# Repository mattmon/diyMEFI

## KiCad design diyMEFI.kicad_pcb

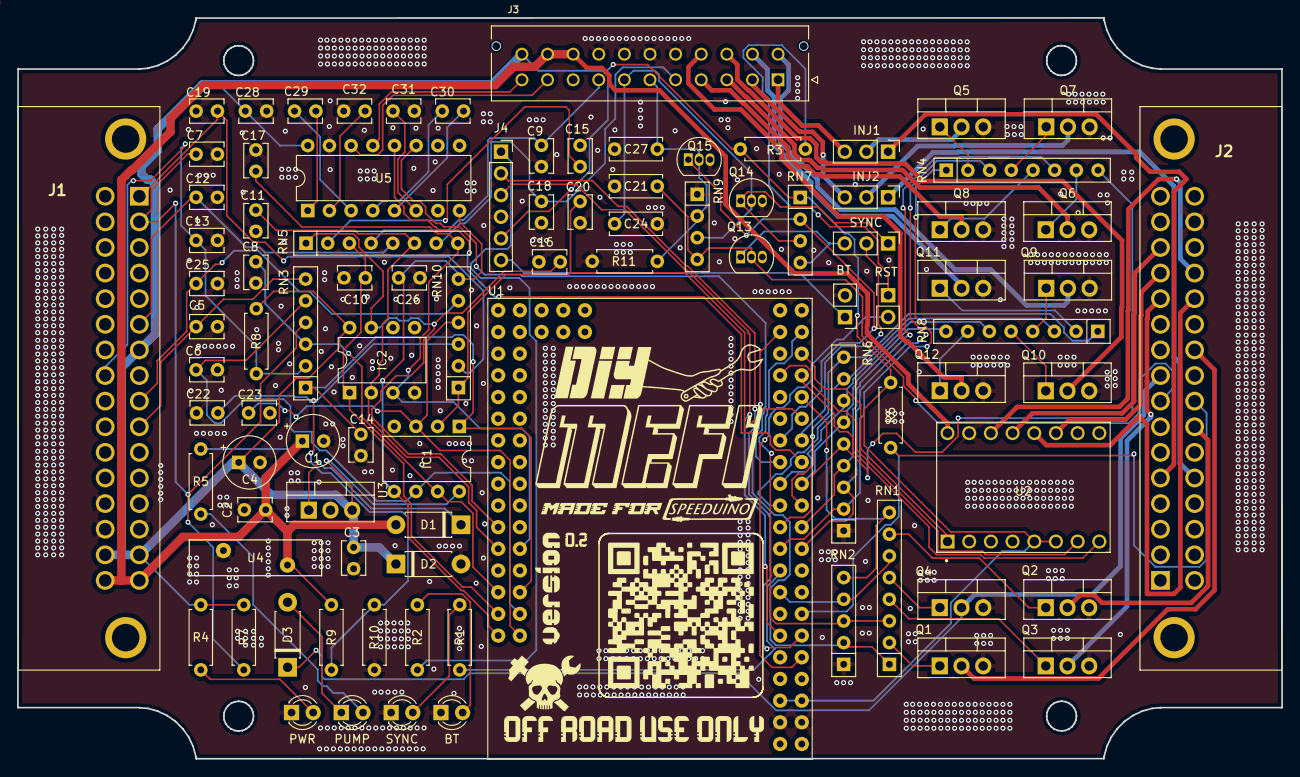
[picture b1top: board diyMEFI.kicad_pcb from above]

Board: 2 copper layers, 148.1 x 86.8 mm, 91 parts (0 on the bottom side), 101 nets.

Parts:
BT: Jumper_2_Open; PinHeader_1x02_P2.54mm_Vertical
BT#2: BLUE; LED_D3.0mm
C1: 10u; CP_Radial_Tantal_D6.0mm_P2.50mm
C2, C3, C5, C7, C9, C12, C13, C15, C18, C19, C22, C25: u1; C_Disc_D3.8mm_W2.6mm_P2.50mm
C4: 47u; CP_Radial_Tantal_D6.0mm_P2.50mm
C6, C8, C10, C11, C14, C16, C17, C20, C23, C26: u22; C_Disc_D3.8mm_W2.6mm_P2.50mm
C21, C24, C27: u1; C_Disc_D6.0mm_W2.5mm_P5.00mm
C28, C29, C30, C31, C32: 1uf; C_Disc_D3.8mm_W2.6mm_P2.50mm
D1: 1N5818; D_DO-41_SOD81_P7.62mm_Horizontal
D2: 1N5919BG; D_DO-41_SOD81_P7.62mm_Horizontal
D3: 1N4004; D_DO-41_SOD81_P7.62mm_Horizontal
IC1, IC2: SP721APP; DIP-8_W7.62mm
INJ1, INJ2: NA; PinHeader_1x03_P2.54mm_Vertical
J1: INPUT; 12129008
J2: OUTPUT; 12129008
J3: EXPANSION; MOLEX_430452227
J4: HC-05; PinSocket_1x06_P2.54mm_Vertical
PUMP: FP; LED_D3.0mm
PWR: RED; LED_D3.0mm
Q1, Q2, Q3, Q4, Q5, Q6, Q7, Q8, Q9, Q10, Q11, Q12: STP62NS04Z; TO-220-3_Vertical
Q13, Q14, Q15: BS170; TO-92_Inline
R1, R2, R4: 220; R_Axial_DIN0207_L6.3mm_D2.5mm_P7.62mm_Horizontal
R3: 56; R_Axial_DIN0207_L6.3mm_D2.5mm_P7.62mm_Horizontal
R5: 2k; R_Axial_DIN0207_L6.3mm_D2.5mm_P7.62mm_Horizontal
R6, R11: 10k; R_Axial_DIN0207_L6.3mm_D2.5mm_P7.62mm_Horizontal
R7, R8: 2k49; R_Axial_DIN0207_L6.3mm_D2.5mm_P7.62mm_Horizontal
R9: 3k9; R_Axial_DIN0207_L6.3mm_D2.5mm_P7.62mm_Horizontal
R10: 1k; R_Axial_DIN0207_L6.3mm_D2.5mm_P7.62mm_Horizontal
RN1, RN4, RN8: 1k; R_Array_SIP8
RN2: 100k; R_Array_SIP5
RN3, RN10: 470; R_Array_SIP6
RN5: 470; R_Array_SIP8
RN6: 100k; R_Array_SIP9
RN7: 1k; R_Array_SIP4
RN9: 10k; R_Array_SIP4
RST: NA; PinHeader_1x02_P2.54mm_Vertical
SYNC: NA; PinHeader_1x03_P2.54mm_Vertical
SYNC#2: YELLOW; LED_D3.0mm
U1: MEGA PRO Embedded; MODULE_MEGA_PRO_EMBED_CH340G___ATMEGA2560
U2: DRV8825; IC_DRV8825_STEPPER_MOTOR_DRIVER_CARRIER
U3: LM2940T-5.0; TO-220-3_Vertical
U4: ERZ; RV_Disc_D15.5mm_W4.2mm_P7.5mm
U5: MAX232; DIP-16_W7.62mm

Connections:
+5V: C3.1, C4.1, C28.1, D2.1 (K), IC1.8, IC2.8, J1.7, J1.15, J1.31, J3.22, J4.5, R3.1, R4.1, R6.1, R7.1, R8.1, RN7.1 (common), U1.5V_1 (5V), U1.5V_2 (5V), U2.5 (~RST), U2.6 (~SLP), U3.3 (VO), U5.16 (VCC)
+12V: C1.1, C2.1, D1.2 (A), J1.16, J1.32, J3.20, J3.21, R5.2, R9.1, U2.16 (VMOT), U4.1
/A0: C26.1, IC1.5, RN10.6 (R3.2), U1.A0, U5.8 (R2IN)
/A1: C23.1, IC1.3, RN10.4 (R2.2), U1.A1
/A2: C10.1, IC2.1, RN5.3 (R2.1), U1.A2
/A3: C6.1, IC1.6, RN3.5 (R3.1), U1.A3
/A4: C8.1, IC1.7, RN3.3 (R2.1), U1.A4
/A5: C14.1, IC1.1, RN3.1 (R1.1), U1.A5
/A8: C11.1, IC2.2, RN5.6 (R3.2), U1.A8
/A9: C17.1, IC2.3, RN5.8 (R4.2), U1.A9
/A10: C16.1, IC2.7, RN5.1 (R1.1), U1.A10
/BUZZER: J2.12, Q3.2 (D)
/BYPASS: J2.24, R6.2, U1.D3
/CAM: C27.1, J3.6, Q15.2 (G), R11.1, RN9.2 (R1)
/CLT: C7.1, J1.2, R7.2, RN3.4 (R2.2)
/CRANK: C24.1, J3.7, Q14.2 (G), RN9.3 (R2)
/D4: RN1.6 (R3.2), RN2.4 (R3), U1.D4
/D8: RN4.1 (R1.1), RN6.2 (R1), U1.D8
/D9: RN4.3 (R2.1), RN6.3 (R2), U1.D9
/D10: RN4.8 (R4.2), RN6.5 (R4), U1.D10
/D11: RN4.6 (R3.2), RN6.4 (R3), U1.D11
/D12: RN6.8 (R7), RN8.3 (R2.1), U1.D12
/D13: RN6.9 (R8), RN8.1 (R1.1), U1.D13
/D14: RN6.7 (R6), RN8.6 (R3.2), U1.D14
/D15: RN6.6 (R5), RN8.8 (R4.2), U1.D15
/D18: Q15.1 (D), RN7.2 (R1), U1.D18
/D19: SYNC.2, U1.D19
/D21: C20.1, IC1.2, RN10.1 (R1.1), U1.D21
/D23: RN1.8 (R4.2), RN2.5 (R4), U1.D23
/D28: RN1.1 (R1.1), RN2.2 (R1), U1.D28
/D29: RN1.3 (R2.1), RN2.3 (R2), U1.D29
/DATA_RX: J3.11, U5.13 (R1IN)
/DATA_TX: J3.10, U5.14 (T1OUT)
/DIR: U1.D25, U2.8 (DIR)
/DIST_HIGH: C21.1, J2.8, Q13.2 (G), RN9.4 (R3)
/ENBL: U1.D27, U2.1 (~EN)
/FP: C18.1, J3.5, RN5.7 (R4.1)
/FUELP: D3.1 (K), J2.9, Q4.2 (D)
/IAT: C13.1, J1.24, R8.2, RN3.2 (R1.2)
/IGN1: J2.23, Q2.2 (D)
/INJ1: INJ2.2, Q5.2 (D)
/INJ1A: INJ2.1, J2.5
/INJ2: INJ1.2, Q7.2 (D)
/INJ2A: INJ1.1, J2.21
/INJ3: J3.3, Q6.2 (D)
/INJ4: J3.4, Q8.2 (D)
/INJ5: J3.12, Q9.2 (D)
/INJ6: J3.13, Q11.2 (D)
/INJ7: J3.14, Q10.2 (D)
/INJ8: J3.15, Q12.2 (D)
/Inputs & Outputs/RESET: RST.2, U1.RST
/KNOCK: C19.1, J1.1, RN10.2 (R1.2)
/MAP: C25.1, J1.9, RN10.5 (R3.1)
/O2A: C9.1, J3.8, RN5.4 (R2.2)
/O2B: C15.1, J3.9, RN5.2 (R1.2)
/OP: C12.1, J1.6, RN5.5 (R3.1)
/RX: J4.3, U1.RX
/RX2: U1.D17, U5.12 (R1OUT)
/STEP: U1.D24, U2.7 (STEP)
/STP-A1: J2.28, U2.12 (A1)
/STP-A2: J2.13, U2.11 (A2)
/STP-B1: J2.14, U2.13 (B1)
/STP-B2: J2.29, U2.14 (B2)
/TPS: C5.1, J1.10, RN3.6 (R3.2)
/TX: J4.2, U1.TX
/TX2: U1.D16, U5.11 (T1IN)
/WARN_LAMP: J2.26, Q1.2 (D)
Earth: BT.2 (B), BT#2.1 (K), C1.2, C2.2, C3.2, C4.2, C5.2, C6.2, C7.2, C8.2, C9.2, C10.2, C11.2, C12.2, C13.2, C14.2, C15.2, C16.2, C17.2, C18.2, C19.2, C20.2, C21.2, C22.2, C23.2, C24.2, C25.2, C26.2, C27.2, C28.2, C31.2, C32.1, D2.2 (A), IC1.4, IC2.4, J1.13, J1.14, J1.29, J1.30, J2.6, J2.15, J2.20, J2.31, J3.16, J3.17, J3.18, J3.19, J4.4, PWR.1 (K), Q1.3 (S), Q2.3 (S), Q3.3 (S), Q4.3 (S), Q5.3 (S), Q6.3 (S), Q7.3 (S), Q8.3 (S), Q9.3 (S), Q10.3 (S), Q11.3 (S), Q12.3 (S), Q13.3 (S), Q14.3 (S), Q15.3 (S), R10.2, R11.2, RN2.1 (common), RN6.1 (common), RN9.1 (common), SYNC#2.1 (K), U1.GND_1 (GND), U1.GND_2 (GND), U2.9 (GND), U2.15 (GND_MOT), U3.2 (GND), U4.2, U5.15 (GND)
unnamed: BT#2.2 (A), R2.2
unnamed: BT.1 (A), J4.6
unnamed: D1.1 (K), U3.1 (VI)
unnamed: D3.2 (A), PUMP.1 (K)
unnamed: PUMP.2 (A), R5.1
unnamed: INJ1.3, J3.2
unnamed: INJ2.3, J3.1
unnamed: J4.1, R2.1
unnamed: PWR.2 (A), R4.2
unnamed: Q1.1 (G), RN1.2 (R1.2)
unnamed: Q2.1 (G), RN1.7 (R4.1)
unnamed: Q3.1 (G), RN1.4 (R2.2)
unnamed: Q4.1 (G), RN1.5 (R3.1)
unnamed: Q5.1 (G), RN4.2 (R1.2)
unnamed: Q6.1 (G), RN4.7 (R4.1)
unnamed: Q7.1 (G), RN4.4 (R2.2)
unnamed: Q8.1 (G), RN4.5 (R3.1)
unnamed: Q9.1 (G), RN8.4 (R2.2)
unnamed: Q10.1 (G), RN8.5 (R3.1)
unnamed: Q11.1 (G), RN8.2 (R1.2)
unnamed: Q12.1 (G), RN8.7 (R4.1)
unnamed: Q13.1 (D), RN7.4 (R3), SYNC.3
unnamed: Q14.1 (D), RN7.3 (R2), SYNC.1
unnamed: R1.1, U1.D6
unnamed: R3.2, RST.1
unnamed: C22.1, R9.2, R10.1, RN10.3 (R2.1)
unnamed: R1.2, SYNC#2.2 (A)
unnamed: C29.2, U5.1 (C1+)
unnamed: C29.1, U5.3 (C1-)
unnamed: C30.2, U5.4 (C2+)
unnamed: C30.1, U5.5 (C2-)
unnamed: C32.2, U5.2 (VS+)
unnamed: C31.1, U5.6 (VS-)

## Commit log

2024-08-25 diyMEFI v0.2
    design and fab files
2024-08-25 added 3d printable 'enclosure'
    the term 'enclosure' used very loosely
2024-08-25 added pdf schematic
    useful for assembly
2024-08-26 added speeduino binary, precompiled for diyMEFI
    O3 compiler optimization
2024-08-26 missed a binary
    oops
2024-08-26 add TunerStudio ini file
    allows for the diyMEFI pinLayout to be selected in Tuner Studio -> Engine Constants
2024-08-26 added msq base tune
    just for hardware setup, don't run an engine from this
2024-08-28 Update diyMEFI-base.msq
    added VE and advance tables extracted from generic LT1 eeprom
2024-08-28 first try at modeling a MEFI connector
    includes printable stl and sketchup source, should be to scale (mm)
2024-08-30 connector with tabs and supports
2024-08-30 stl with the improved support (same as skp)
2025-02-01 add malibu call dir
